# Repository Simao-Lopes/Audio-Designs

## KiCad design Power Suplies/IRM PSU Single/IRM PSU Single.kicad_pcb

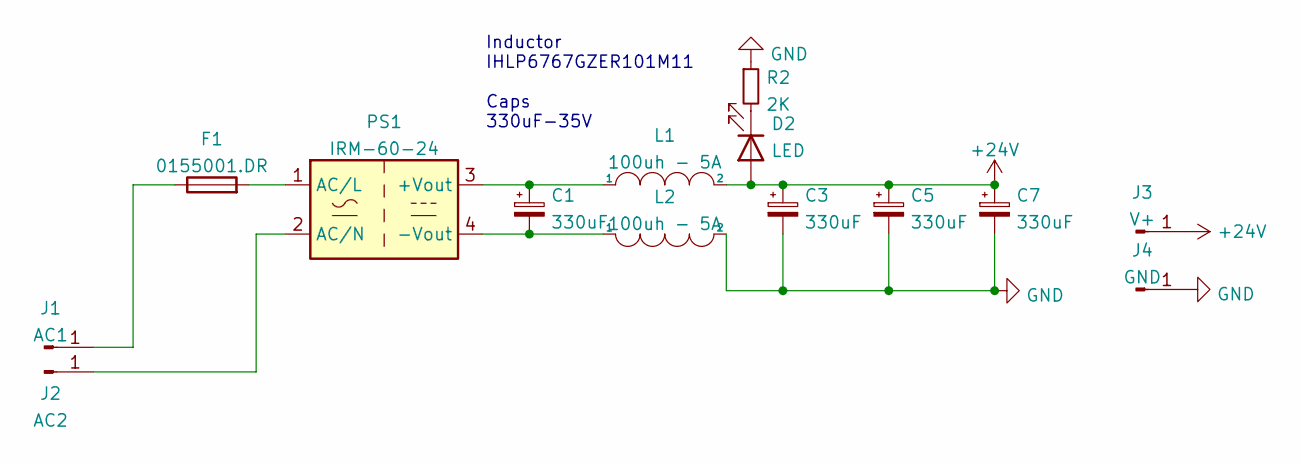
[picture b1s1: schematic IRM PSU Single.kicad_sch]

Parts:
C1, C3, C5, C7: 330uF; CP_Elec_16x17.5
D2: LED; LED_1210_3225Metric
F1: 0155001.DR; Fuseholder_Littelfuse_100_series_5x20mm
J1: AC1; Spade Conector 6.3mm TE_1217861
J2: AC2; Spade Conector 6.3mm TE_1217861
J3: V+; Spade Conector 6.3mm TE_1217861
J4: GND; Spade Conector 6.3mm TE_1217861
L1, L2: 100uh - 5A; L_Vishay_IHLP-6767
PS1: IRM-60-24; Converter_ACDC_MeanWell_IRM-60-xx_THT
R2: 2K; R_1210_3225Metric

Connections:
+24V: C3.1, C5.1, C7.1, D2.2 (A), J3.1, L1.2
GND: C3.2, C5.2, C7.2, J4.1, L2.2, R2.1
unnamed: C1.1, L1.1, PS1.3 (+Vout)
unnamed: C1.2, L2.1, PS1.4 (-Vout)
unnamed: D2.1 (K), R2.2
unnamed: F1.1, J1.1
unnamed: F1.2, PS1.1 (AC/L)
unnamed: J2.1, PS1.2 (AC/N)

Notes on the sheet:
Inductor IHLP6767GZER101M11 Caps 330uF-35V

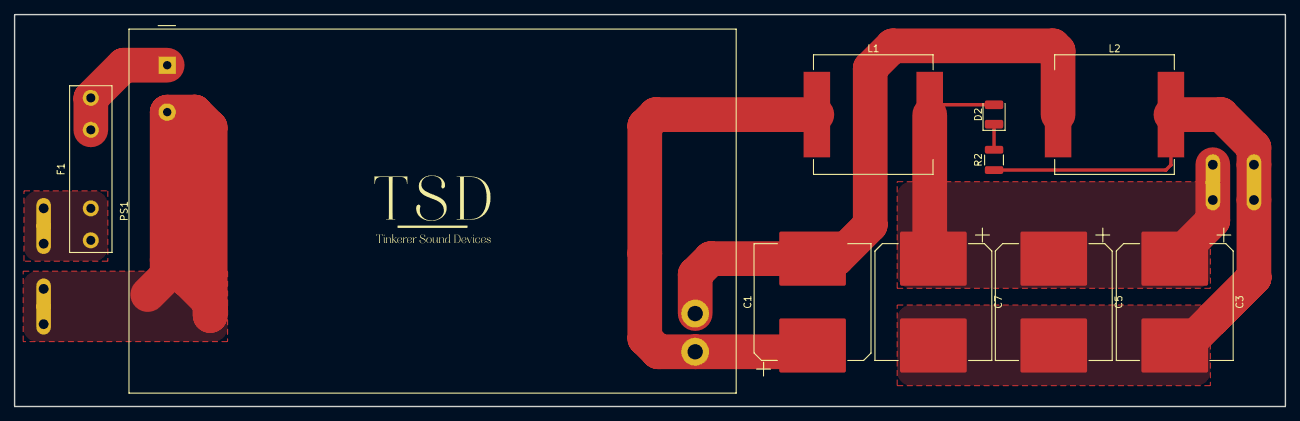
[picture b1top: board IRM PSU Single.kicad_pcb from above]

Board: 2 copper layers, 182.9 x 56.4 mm, 14 parts (0 on the bottom side), 8 nets.

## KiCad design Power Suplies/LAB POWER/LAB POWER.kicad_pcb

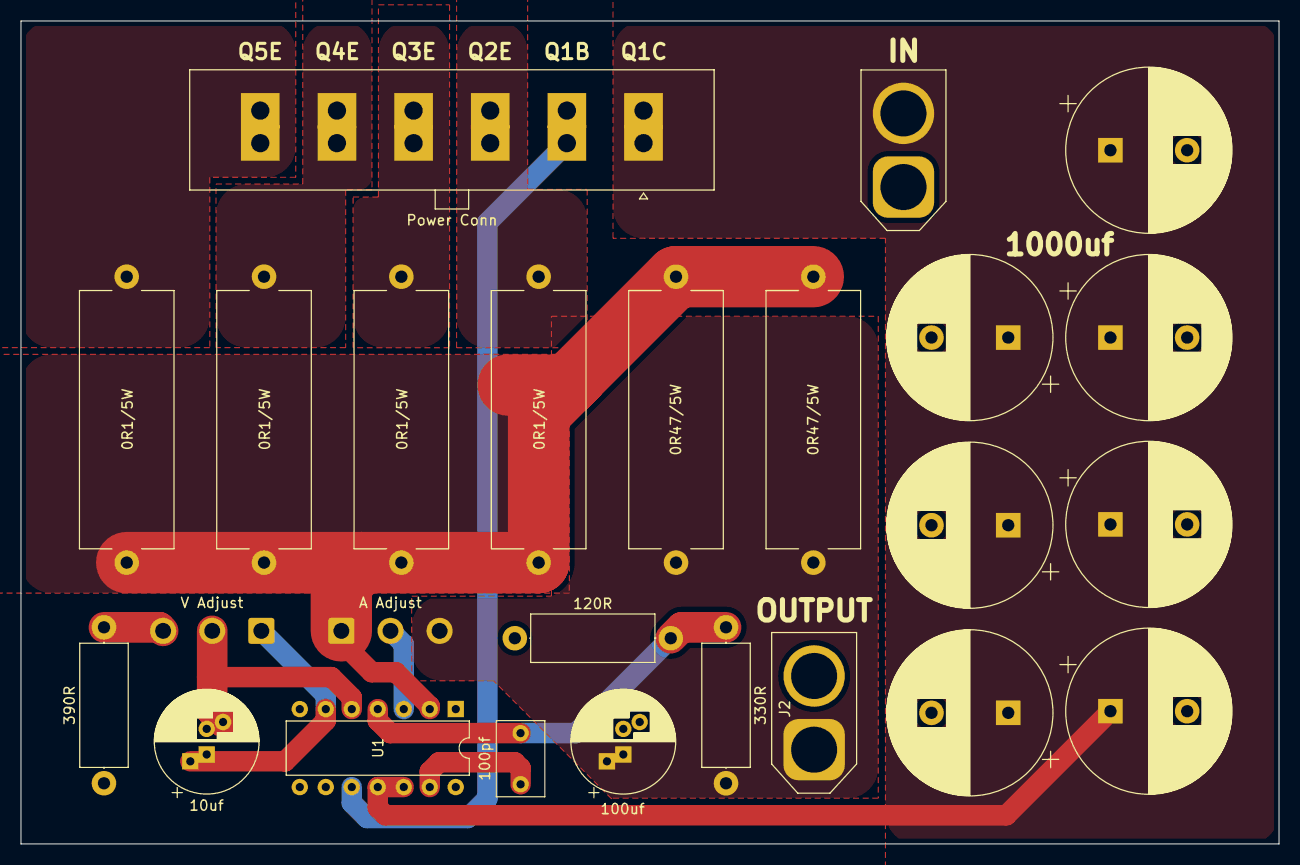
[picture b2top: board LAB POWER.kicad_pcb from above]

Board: 2 copper layers, 122.9 x 80.4 mm, 25 parts (0 on the bottom side), 15 nets.

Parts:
A Adjust: 500R; SolderWire-0.75sqmm_1x03_P4.8mm_D1.25mm_OD2.3mm
C1, C2, C3, C4, C5, C7, C8: 1000uf; CP_Radial_D16.0mm_P7.50mm
C6: 10uf; CP_Radial_D10.0mm_P2.50mm_P5.00mm
C9: 100pf; C_Rect_L7.2mm_W4.5mm_P5.00mm_FKS2_FKP2_MKS2_MKP2
C10: 100uf; CP_Radial_D10.0mm_P2.50mm_P5.00mm
J1: IN; AMASS_XT60-M_1x02_P7.20mm_Vertical
J2: OUTPUT; AMASS_XT60-M_1x02_P7.20mm_Vertical
Power Conn: Q_CONN; Molex_Sabre_43160-0106_1x06_P7.49mm_Vertical
R1: 390R; R_Axial_DIN0414_L11.9mm_D4.5mm_P15.24mm_Horizontal
R2: 120R; R_Axial_DIN0414_L11.9mm_D4.5mm_P15.24mm_Horizontal
R3: 330R; R_Axial_DIN0414_L11.9mm_D4.5mm_P15.24mm_Horizontal
R4, R5, R6, R7: 0R1/5W; R_Axial_Power_L25.0mm_W9.0mm_P27.94mm
R8, R9: 0R47/5W; R_Axial_Power_L25.0mm_W9.0mm_P27.94mm
U1: LM723_DIP14; DIP-14_W7.62mm
V Adjust: 5k; SolderWire-0.75sqmm_1x03_P4.8mm_D1.25mm_OD2.3mm

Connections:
/+: A Adjust.3, C10.1, J2.1, R3.1, R8.1, R9.1
/A_Adj: A Adjust.1, R4.2, R5.2, R6.2, R7.2, R8.2, R9.2, U1.2 (ILIM)
/Q1B: Power Conn.2, U1.10 (Vout)
/Q1C: C1.1, C2.1, C3.1, C4.1, C5.1, C7.1, C8.1, J1.2, Power Conn.1, U1.11 (VC), U1.12 (V+)
/Q2E: Power Conn.3, R4.1
/Q3E: Power Conn.4, R5.1
/Q4E: Power Conn.5, R6.1
/Q5E: Power Conn.6, R7.1
/V_Adj: C6.1, U1.6 (VREF), V Adjust.1
GND: C1.2, C2.2, C3.2, C4.2, C5.2, C7.2, C8.2, C10.2, J1.1, J2.2, R1.2, R2.2, U1.7 (V-)
unnamed: C6.2, U1.5 (+), V Adjust.2
unnamed: C9.1, R2.1, R3.2, U1.4 (-)
unnamed: C9.2, U1.13 (FC)
unnamed: R1.1, V Adjust.3
unnamed: A Adjust.2, U1.3 (CSEN)

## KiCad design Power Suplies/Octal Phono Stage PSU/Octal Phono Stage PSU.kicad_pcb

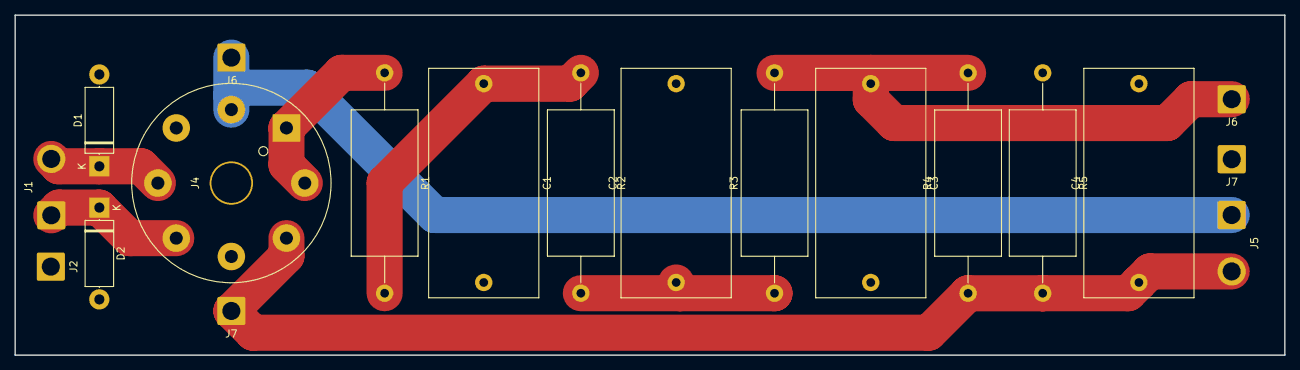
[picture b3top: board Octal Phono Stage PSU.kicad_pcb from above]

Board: 2 copper layers, 175.6 x 47.0 mm, 19 parts (0 on the bottom side), 9 nets.

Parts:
C1, C2, C3, C4: C; C_Rect_L31.5mm_W15.0mm_P27.50mm_MKS4
D1, D2: uf4007; D_5W_P12.70mm_Horizontal
J1: 300Vac; SolderWire-2sqmm_1x02_P7.8mm_D2mm_OD3.9mm
J2: Gnd Ac; SolderWire-2sqmm_1x01_D2mm_OD3.9mm
J4: 6BY5; Valve_Octal
J5: Heater; SolderWire-2sqmm_1x02_P7.8mm_D2mm_OD3.9mm
J6: 350V; SolderWire-2sqmm_1x01_D2mm_OD3.9mm
J6#2, J7: 6.3Vac; SolderWire-2sqmm_1x01_D2mm_OD3.9mm
J7#2: Gnd 350V; SolderWire-2sqmm_1x01_D2mm_OD3.9mm
R1: 250; R_Axial_DIN0922_L20.0mm_D9.0mm_P30.48mm_Horizontal
R2, R3: 500; R_Axial_DIN0922_L20.0mm_D9.0mm_P30.48mm_Horizontal
R4: 100K; R_Axial_DIN0922_L20.0mm_D9.0mm_P30.48mm_Horizontal
R5: 10K; R_Axial_DIN0922_L20.0mm_D9.0mm_P30.48mm_Horizontal

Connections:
GND: C1.2, C2.2, C3.2, C4.2, D1.2 (A), D2.2 (A), J2.1, J7#2.1, R5.1
unnamed: C1.1, R1.2, R2.1
unnamed: C2.1, R2.2, R3.1
unnamed: C3.1, J6.1, R3.2, R4.2
unnamed: C4.1, J4.7, J5.2, J7.1, R4.1, R5.2
unnamed: D1.1 (K), J1.2, J4.4
unnamed: D2.1 (K), J1.1, J4.5
unnamed: J4.2, J5.1, J6#2.1
unnamed: J4.1, J4.8, R1.1

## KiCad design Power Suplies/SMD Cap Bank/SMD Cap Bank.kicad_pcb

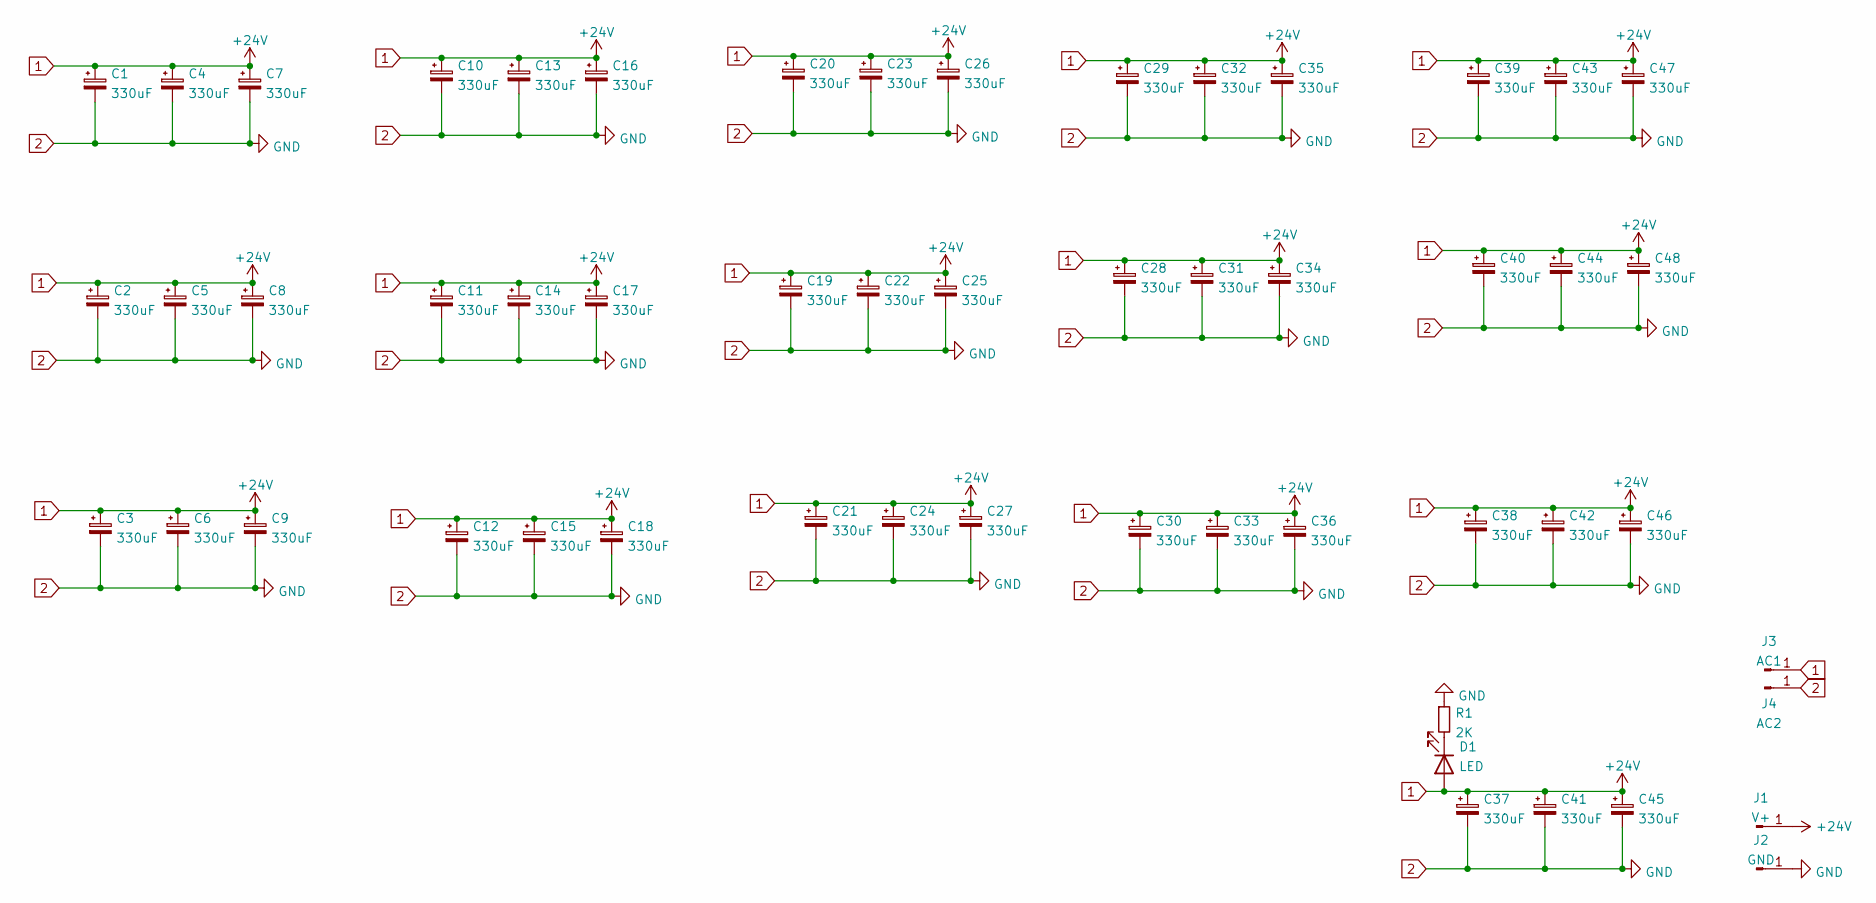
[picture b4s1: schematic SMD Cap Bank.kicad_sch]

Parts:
C1, C2, C3, C4, C5, C6, C7, C8, C9, C10, C11, C12, C13, C14, C15, C16, C17, C18, C19, C20, C21, C22, C23, C24, C25, C26, C27, C28, C29, C30, C31, C32, C33, C34, C35, C36, C37, C38, C39, C40, C41, C42, C43, C44, C45, C46, C47, C48: 330uF; CP_Elec_16x17.5
D1: LED; LED_1210_3225Metric
J1: V+; Spade Conector 6.3mm TE_1217861
J2: GND; Spade Conector 6.3mm TE_1217861
J3: AC1; Spade Conector 6.3mm TE_1217861
J4: AC2; Spade Conector 6.3mm TE_1217861
R1: 2K; R_1210_3225Metric

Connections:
1: C1.1, C2.1, C3.1, C4.1, C5.1, C6.1, C7.1, C8.1, C9.1, C10.1, C11.1, C12.1, C13.1, C14.1, C15.1, C16.1, C17.1, C18.1, C19.1, C20.1, C21.1, C22.1, C23.1, C24.1, C25.1, C26.1, C27.1, C28.1, C29.1, C30.1, C31.1, C32.1, C33.1, C34.1, C35.1, C36.1, C37.1, C38.1, C39.1, C40.1, C41.1, C42.1, C43.1, C44.1, C45.1, C46.1, C47.1, C48.1, D1.2 (A), J1.1, J3.1
2: C1.2, C2.2, C3.2, C4.2, C5.2, C6.2, C7.2, C8.2, C9.2, C10.2, C11.2, C12.2, C13.2, C14.2, C15.2, C16.2, C17.2, C18.2, C19.2, C20.2, C21.2, C22.2, C23.2, C24.2, C25.2, C26.2, C27.2, C28.2, C29.2, C30.2, C31.2, C32.2, C33.2, C34.2, C35.2, C36.2, C37.2, C38.2, C39.2, C40.2, C41.2, C42.2, C43.2, C44.2, C45.2, C46.2, C47.2, C48.2, J2.1, J4.1, R1.1
unnamed: D1.1 (K), R1.2

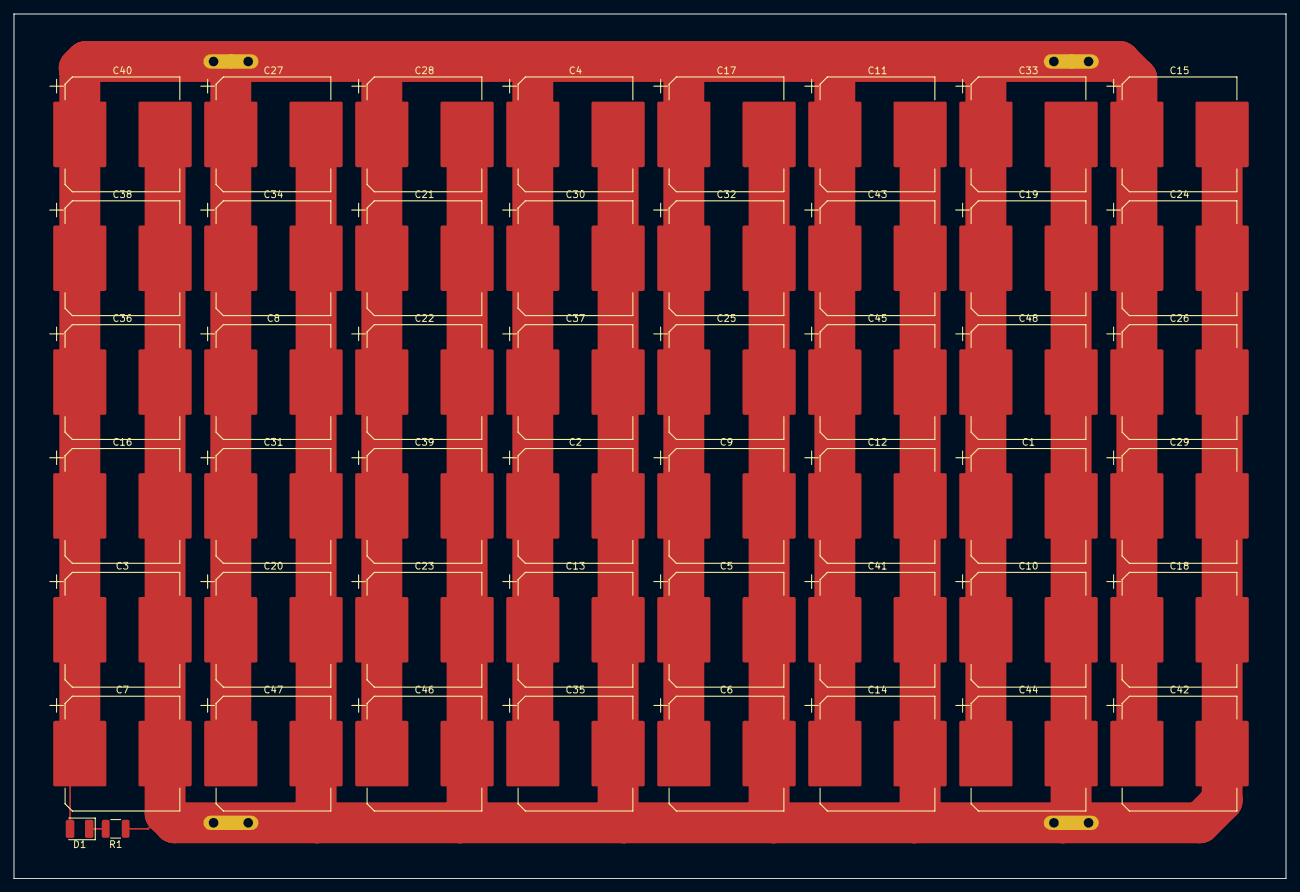
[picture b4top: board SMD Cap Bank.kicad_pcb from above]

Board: 2 copper layers, 186.4 x 126.7 mm, 54 parts (0 on the bottom side), 3 nets.
